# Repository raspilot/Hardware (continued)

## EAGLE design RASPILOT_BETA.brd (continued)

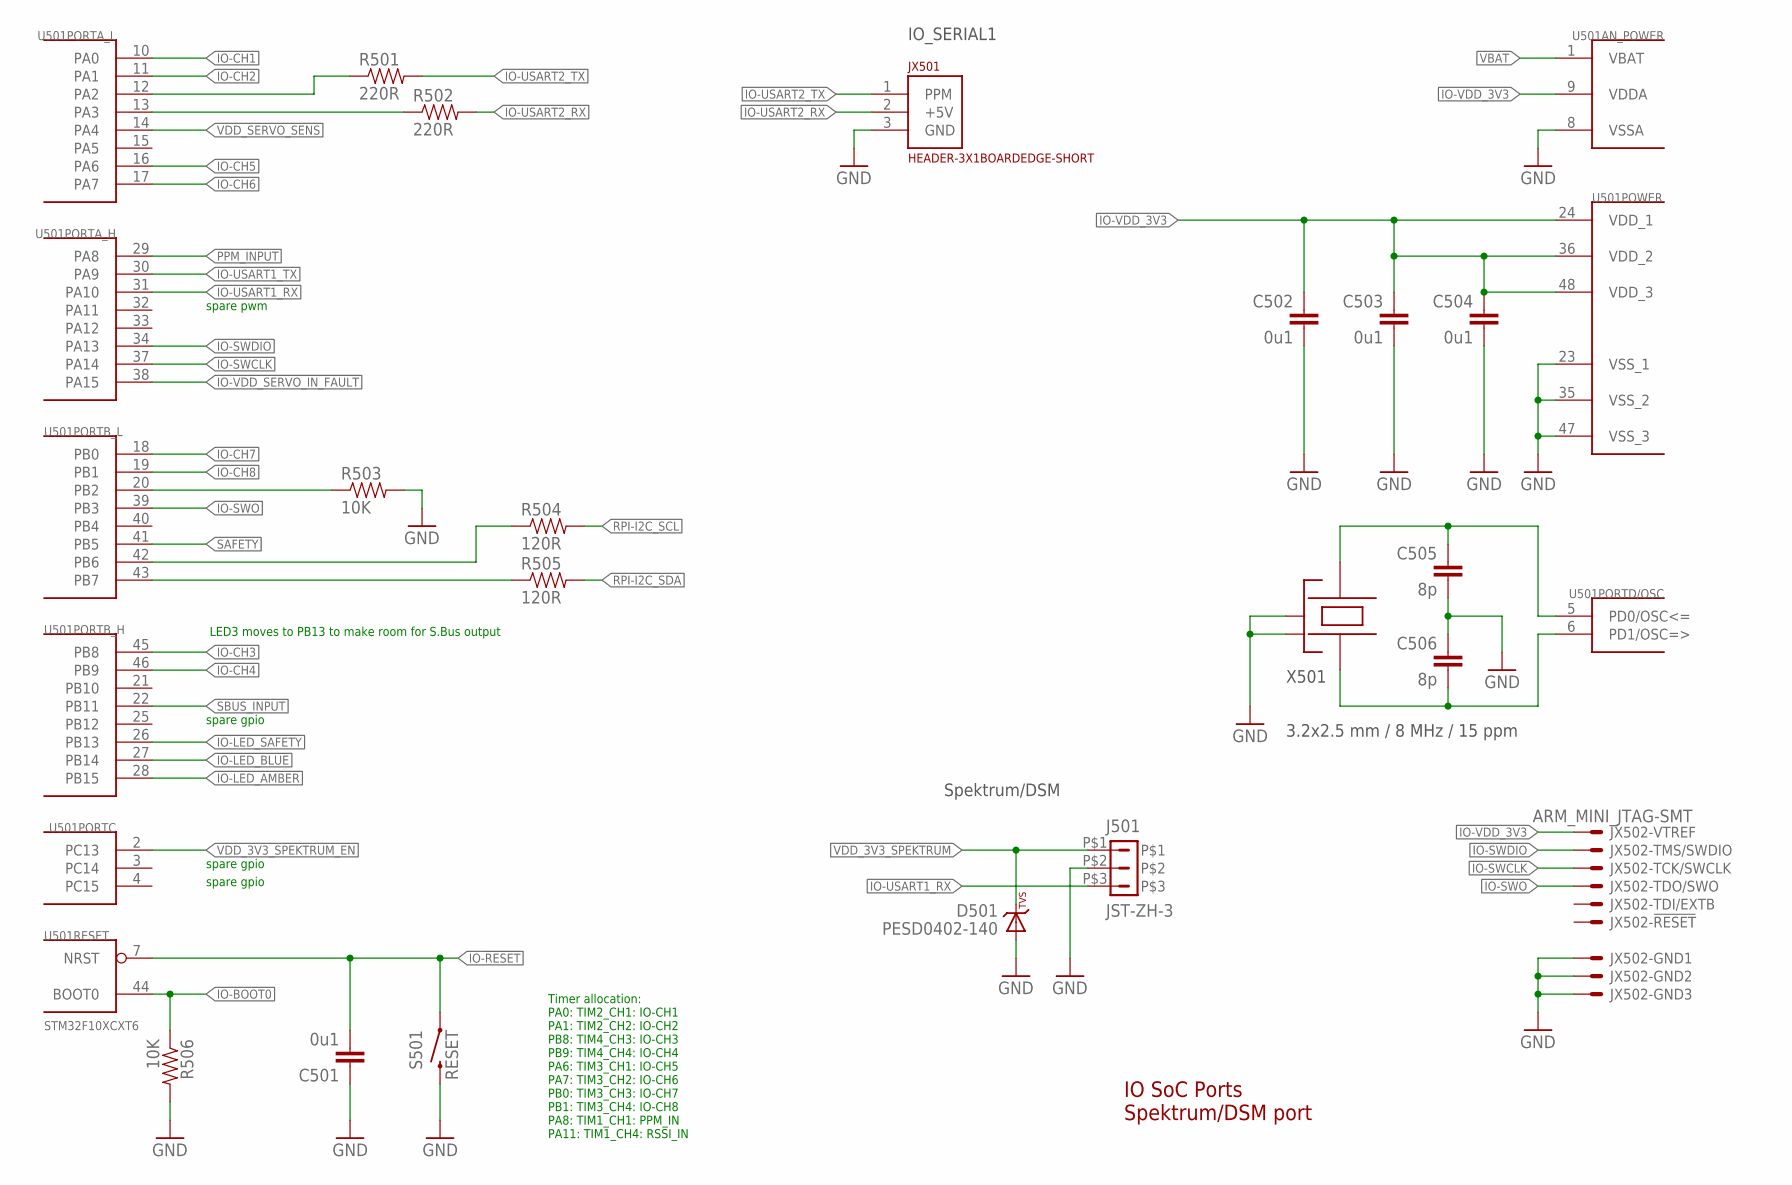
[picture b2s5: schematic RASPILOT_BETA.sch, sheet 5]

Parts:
C501, C502, C503, C504: 0u1; 0402-CAP; PARTNO CC0402ZRY5V7BB104
C505, C506: 8p; 0402-CAP; PARTNO C1005C0G1H080C
D501: PESD0402-140; 0402-TVS; PARTNO PESD0402-140
J501: JST-ZH-3; JST-ZH-SMT-VERTICAL; PARTNO B3B-ZR-SM4-TF (LF)(SN)(P)
JX501: HEADER-3X1BOARDEDGE-SHORT; HEADER_3X01_SMD_H_BOARD_EDGE_SHORT
JX502: ARM_MINI_JTAG-SMT; FTSH-105-01-XXX-DV-K; PARTNO M50-3900542
R501, R502: 220R; 0402-RES; PARTNO RC0402FR-07220RL
R503, R506: 10K; 0402-RES; PARTNO RC0402FR-0710KL
R504, R505: 120R; 0402-RES; PARTNO RC0402FR-07220RL
S501: RESET; EVQP7J01K; PARTNO EVQ-P7J01P
U501: STM32F10XCXT6; TQFP48; PARTNO STM32F100C8T6B
X501: 3.2x2.5 mm / 8 MHz / 15 ppm; OSCILLATOR-3.2X2.5; PARTNO NX3225SA-24.000000MHZ

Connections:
!IO-LED_AMBER: U501.28 (PB15); also elsewhere on the board
!IO-LED_BLUE: U501.27 (PB14); also elsewhere on the board
!IO-LED_SAFETY: U501.26 (PB13); also elsewhere on the board
GND: C501.P$1 (1), C502.P$2 (2), C503.P$2 (2), C504.P$2 (2), C505.P$2 (2), C506.P$1 (1), D501.A, J501.P$2, JX501.3 (GND), JX502.3, JX502.5, JX502.9, R503.P$2 (2), R506.P$2 (2), S501.B3 (2), U501.8 (VSSA), U501.23 (VSS_1), U501.35 (VSS_2), U501.47 (VSS_3), X501.2 (NC_2), X501.4 (NC_4); also elsewhere on the board
IO-!RESET: C501.P$2 (2), S501.A1 (1), U501.7 (NRST); also elsewhere on the board
IO-!VDD_SERVO_IN_FAULT: U501.38 (PA15); also elsewhere on the board
IO-BOOT0: R506.P$1 (1), U501.44 (BOOT0); also elsewhere on the board
IO-BOOT1: R503.P$1 (1), U501.20 (PB2)
IO-CH1: U501.10 (PA0); also elsewhere on the board
IO-CH2: U501.11 (PA1); also elsewhere on the board
IO-CH3: U501.45 (PB8); also elsewhere on the board
IO-CH4: U501.46 (PB9); also elsewhere on the board
IO-CH5: U501.16 (PA6); also elsewhere on the board
IO-CH6: U501.17 (PA7); also elsewhere on the board
IO-CH7: U501.18 (PB0); also elsewhere on the board
IO-CH8: U501.19 (PB1); also elsewhere on the board
IO-SWCLK: JX502.4, U501.37 (PA14)
IO-SWDIO: JX502.2, U501.34 (PA13)
IO-SWO: JX502.6, U501.39 (PB3)
IO-USART1_RX: J501.P$3, U501.31 (PA10)
IO-USART1_TX: U501.30 (PA9)
IO-USART2_RX: JX501.2 (+5V), R502.P$2 (2)
IO-USART2_TX: JX501.1 (PPM), R501.P$2 (2)
IO-VDD_3V3: C502.P$1 (1), C503.P$1 (1), C504.P$1 (1), JX502.1, U501.9 (VDDA), U501.24 (VDD_1), U501.36 (VDD_2), U501.48 (VDD_3); also elsewhere on the board
unnamed: R505.P$1 (1), U501.43 (PB7)
unnamed: R504.P$1 (1), U501.42 (PB6)
unnamed: C506.P$2 (2), U501.6 (PD1/OSC=>), X501.1
unnamed: C505.P$1 (1), U501.5 (PD0/OSC<=), X501.3
unnamed: R501.P$1 (1), U501.12 (PA2)
unnamed: R502.P$1 (1), U501.13 (PA3)
PPM_INPUT: U501.29 (PA8); also elsewhere on the board
RPI-I2C_SCL: R504.P$2 (2); also elsewhere on the board
RPI-I2C_SDA: R505.P$2 (2); also elsewhere on the board
SAFETY: U501.41 (PB5); also elsewhere on the board
SBUS_INPUT: U501.22 (PB11); also elsewhere on the board
VBAT: U501.1 (VBAT)
VDD_3V3_SPEKTRUM: D501.C, J501.P$1; also elsewhere on the board
VDD_3V3_SPEKTRUM_EN: U501.2 (PC13); also elsewhere on the board
VDD_SERVO_SENS: U501.14 (PA4); also elsewhere on the board

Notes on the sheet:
IO SoC Ports Spektrum/DSM port
LED3 moves to PB13 to make room for S.Bus output
IO_SERIAL1
Spektrum/DSM
Timer allocation: PA0: TIM2_CH1: IO-CH1 PA1: TIM2_CH2: IO-CH2 PB8: TIM4_CH3: IO-CH3 PB9: TIM4_CH4: IO-CH4 PA6: TIM3_CH1: IO-CH5 PA7: TIM3_CH2: IO-CH6 PB0: TIM3_CH3: IO-CH7 PB1: TIM3_CH4: IO-CH8 PA8: TIM1_CH1: PPM_IN PA11: TIM1_CH4: RSSI_IN
spare pwm
spare gpio

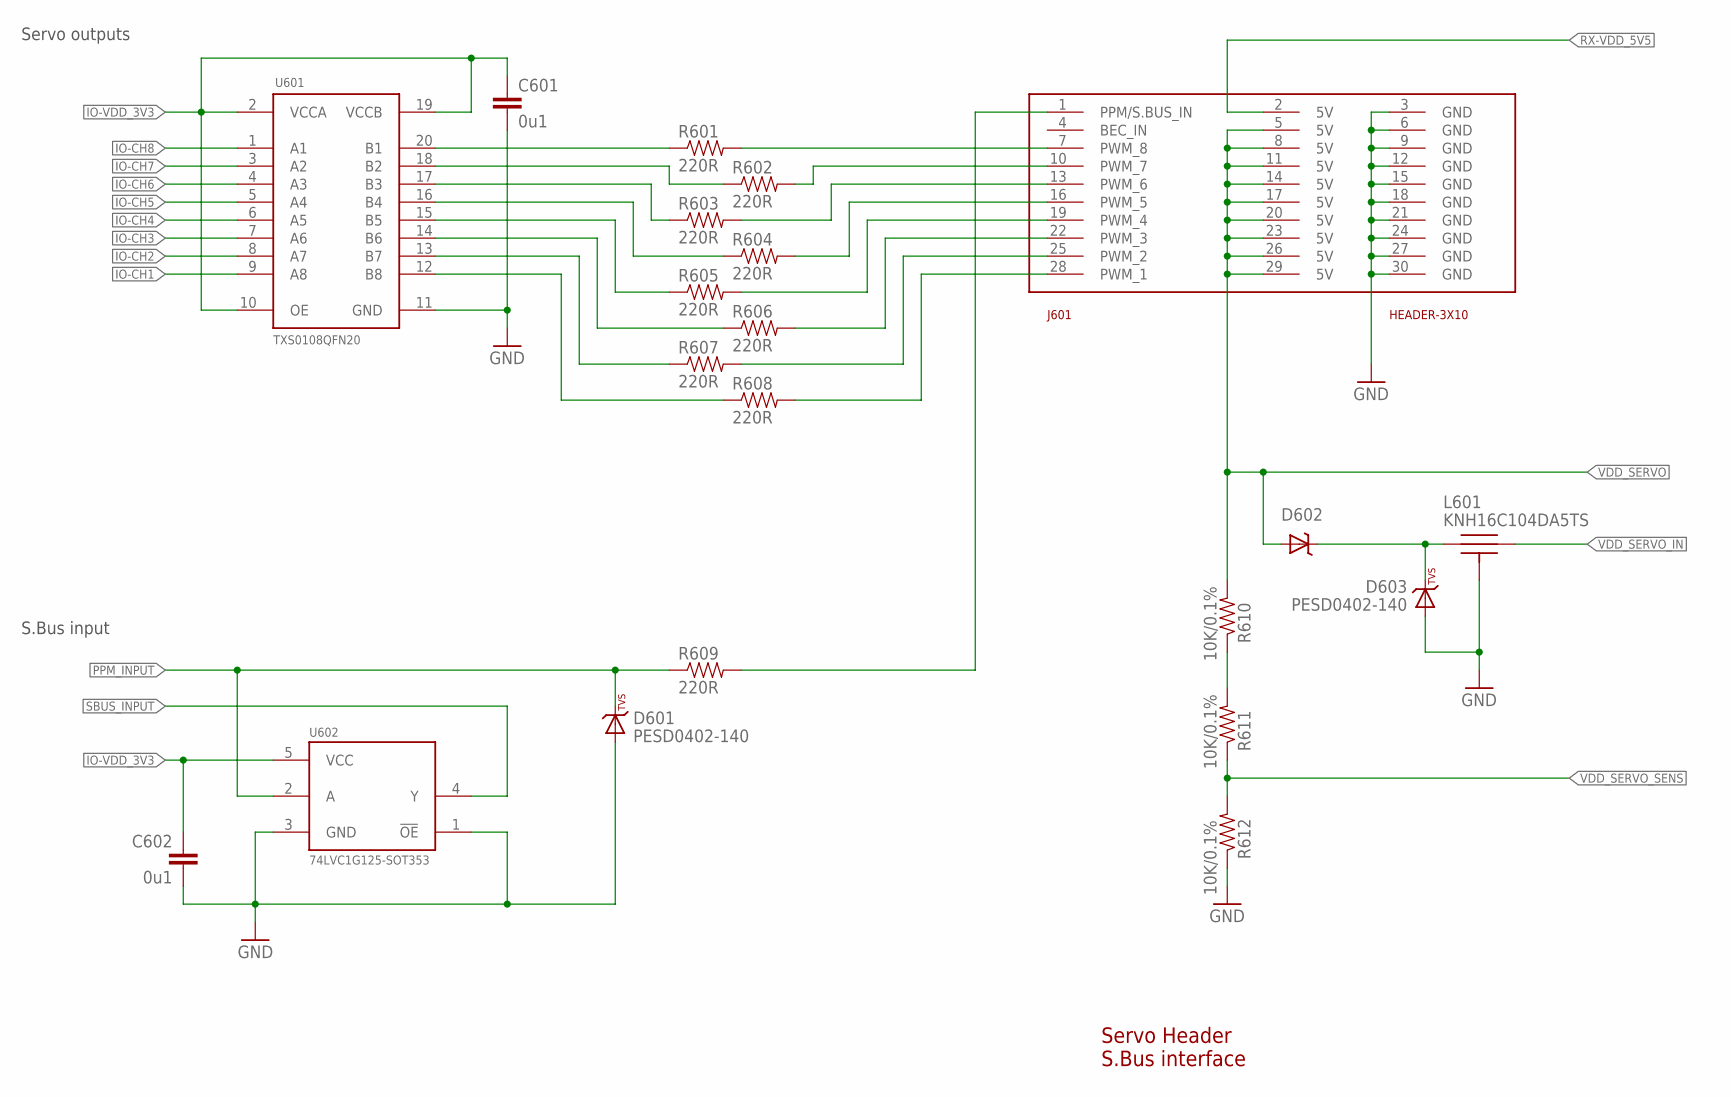
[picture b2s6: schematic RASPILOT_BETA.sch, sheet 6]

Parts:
C601, C602: 0u1; 0402-CAP; PARTNO CC0402ZRY5V7BB104
D601, D603: PESD0402-140; 0402-TVS; PARTNO PESD0402-140
D602: MSS1P4-M3; MICROSMP; PARTNO MSS1P4-M3/89A
J601: HEADER-3X10; 3X10RA
L601: KNH16C104DA5TS; KYOCERA-KNH16-DA; PARTNO KNH16C104DA5TS
R601, R602, R603, R604, R605, R606, R607, R608, R609: 220R; 0402-RES; PARTNO RC0402FR-07220RL
R610, R611, R612: 10K/0.1%; 0402-RES; PARTNO ERA-2AEB103X
U601: TXS0108QFN20; QFN20-RGY; PARTNO TXS0108ERGYR
U602: 74LVC1G125-SOT353; SOT353

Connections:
GND: C601.P$2 (2), C602.P$2 (2), D601.A, D603.A, J601.3 (GND), J601.6 (GND), J601.9 (GND), J601.12 (GND), J601.15 (GND), J601.18 (GND), J601.21 (GND), J601.24 (GND), J601.27 (GND), J601.30 (GND), L601.P$3, L601.P$4, L601.P$5, R612.P$1 (1), U601.11 (GND), U602.1 (!OE), U602.3 (GND); also elsewhere on the board
IO-CH1: U601.9 (A8); also elsewhere on the board
IO-CH2: U601.8 (A7); also elsewhere on the board
IO-CH3: U601.7 (A6); also elsewhere on the board
IO-CH4: U601.6 (A5); also elsewhere on the board
IO-CH5: U601.5 (A4); also elsewhere on the board
IO-CH6: U601.4 (A3); also elsewhere on the board
IO-CH7: U601.3 (A2); also elsewhere on the board
IO-CH8: U601.1 (A1); also elsewhere on the board
IO-VDD_3V3: C601.P$1 (1), C602.P$1 (1), U601.2 (VCCA), U601.10 (OE), U601.19 (VCCB), U602.5 (VCC); also elsewhere on the board
unnamed: R610.P$1 (1), R611.P$2 (2)
unnamed: J601.7 (PWM_8), R601.P$2 (2)
unnamed: R601.P$1 (1), U601.20 (B1)
unnamed: R602.P$1 (1), U601.18 (B2)
unnamed: R603.P$1 (1), U601.17 (B3)
unnamed: R604.P$1 (1), U601.16 (B4)
unnamed: R605.P$1 (1), U601.15 (B5)
unnamed: R606.P$1 (1), U601.14 (B6)
unnamed: R607.P$1 (1), U601.13 (B7)
unnamed: R608.P$1 (1), U601.12 (B8)
unnamed: J601.10 (PWM_7), R602.P$2 (2)
unnamed: J601.28 (PWM_1), R608.P$2 (2)
unnamed: J601.25 (PWM_2), R607.P$2 (2)
unnamed: J601.22 (PWM_3), R606.P$2 (2)
unnamed: J601.19 (PWM_4), R605.P$2 (2)
unnamed: J601.16 (PWM_5), R604.P$2 (2)
unnamed: J601.13 (PWM_6), R603.P$2 (2)
unnamed: D602.CATHODE (C), D603.C, L601.P$1
PPM-SBUS-PROT: J601.1 (PPM/S.BUS_IN), R609.P$2 (2)
PPM_INPUT: D601.C, R609.P$1 (1), U602.2 (A); also elsewhere on the board
RX-VDD_5V5: J601.2 (5V); also elsewhere on the board
SBUS_INPUT: U602.4 (Y); also elsewhere on the board
VDD_SERVO: D602.ANODE (A), J601.5 (5V), J601.8 (5V), J601.11 (5V), J601.14 (5V), J601.17 (5V), J601.20 (5V), J601.23 (5V), J601.26 (5V), J601.29 (5V), R610.P$2 (2); also elsewhere on the board
VDD_SERVO_IN: L601.P$2; also elsewhere on the board
VDD_SERVO_SENS: R611.P$1 (1), R612.P$2 (2); also elsewhere on the board

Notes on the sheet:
Servo Header S.Bus interface
S.Bus input
Servo outputs

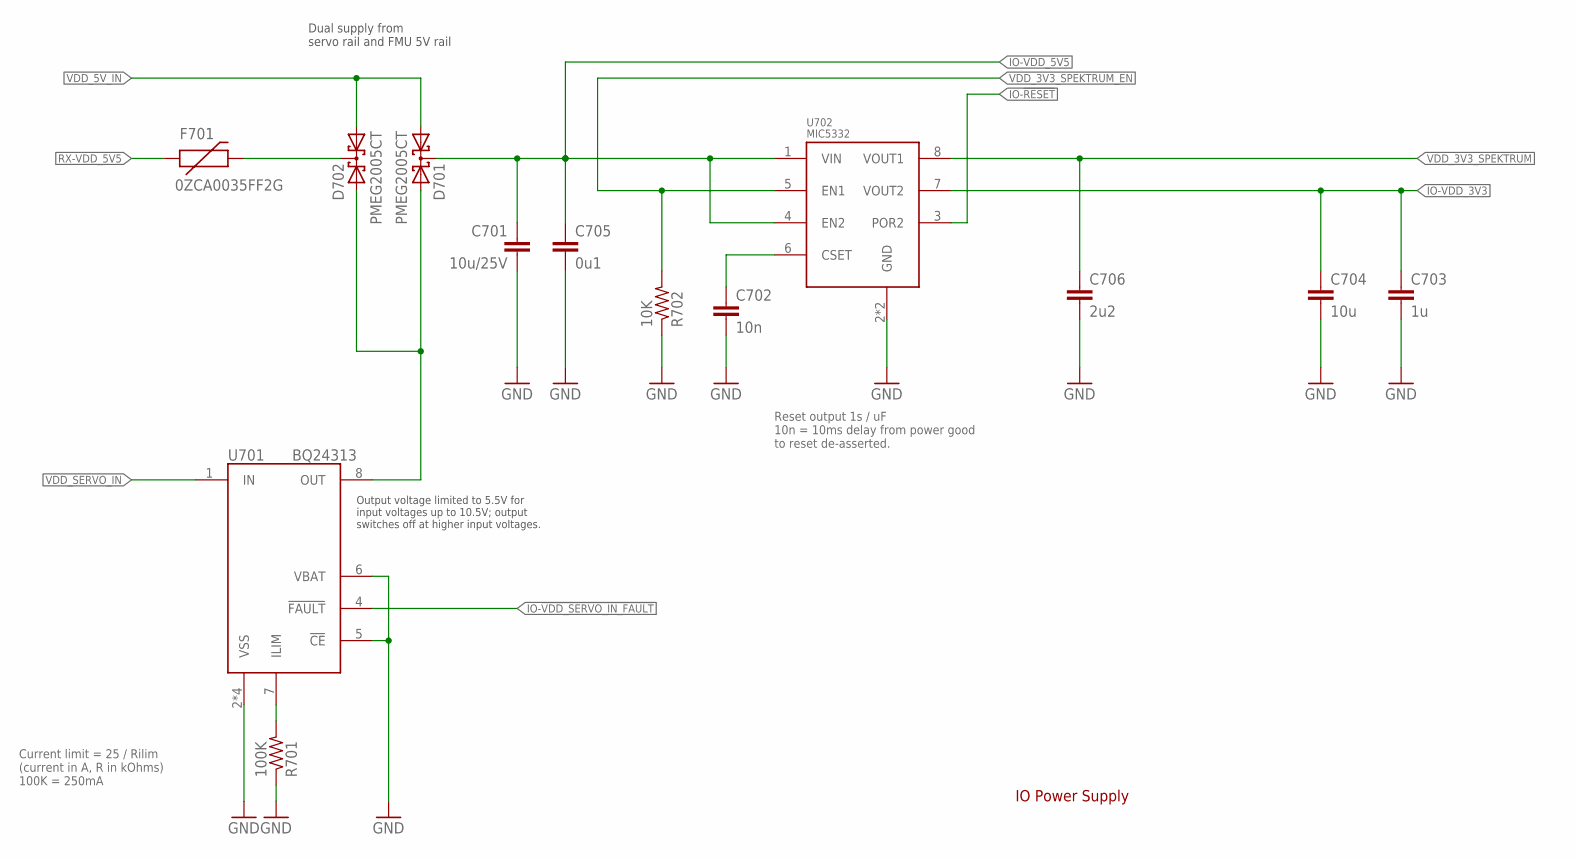
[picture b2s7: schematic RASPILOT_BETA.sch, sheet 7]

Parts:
C701: 10u/25V; 0805-CAP; PARTNO CL21A106KAYNNNE
C702: 10n; 0402-CAP; PARTNO CC0402KRX7R7BB103
C703: 1u; 0603-CAP; PARTNO CC0603ZRY5V7BB105
C704: 10u; 0603-CAP; PARTNO C1608X5R1A106K080AC
C705: 0u1; 0402-CAP; PARTNO CC0402ZRY5V7BB104
C706: 2u2; 0402-CAP; PARTNO C1005X6S1C225K050BC
D701, D702: PMEG2005CT; SOT23-3; PARTNO PMEG2005CT
F701: 0ZCA0035FF2G; PTC-1206; PARTNO 0ZCA0035FF2G
R701: 100K; 0402-RES; PARTNO RC0402FR-07100KL
R702: 10K; 0402-RES; PARTNO RC0402FR-0710KL
U701: BQ24313; QFN8-DSG; PARTNO BQ24313DSGT
U702: MIC5332; MLF-8-EPAD; PARTNO MIC5332-SSYMT

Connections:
GND: C701.P$2 (2), C702.P$2 (2), C703.P$2 (2), C704.P$2 (2), C705.P$2 (2), C706.P$2 (2), R701.P$1 (1), R702.P$1 (1), U701.2 (VSS), U701.5 (!CE), U701.6 (VBAT), U701.GND (VSS), U701.P$2 (VSS), U701.P$3 (VSS), U702.2 (GND), U702.GND; also elsewhere on the board
IO-!RESET: U702.3 (POR2); also elsewhere on the board
IO-!VDD_SERVO_IN_FAULT: U701.4 (!FAULT); also elsewhere on the board
IO-VDD_3V3: C703.P$1 (1), C704.P$1 (1), U702.7 (VOUT2); also elsewhere on the board
IO-VDD_5V5: C701.P$1 (1), C705.P$1 (1), D701.3 (CC), U702.1 (VIN), U702.4 (EN2); also elsewhere on the board
unnamed: D701.2 (A2), D702.2 (A2), U701.8 (OUT)
unnamed: R701.P$2 (2), U701.7 (ILIM)
unnamed: D702.3 (CC), F701.2
unnamed: C702.P$1 (1), U702.6 (CSET)
RX-VDD_5V5: F701.1; also elsewhere on the board
VDD_3V3_SPEKTRUM: C706.P$1 (1), U702.8 (VOUT1); also elsewhere on the board
VDD_3V3_SPEKTRUM_EN: R702.P$2 (2), U702.5 (EN1); also elsewhere on the board
VDD_5V_IN: D701.1 (A1), D702.1 (A1); also elsewhere on the board
VDD_SERVO_IN: U701.1 (IN); also elsewhere on the board

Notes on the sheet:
Dual supply from servo rail and FMU 5V rail
Current limit = 25 / Rilim (current in A, R in kOhms) 100K = 250mA
IO Power Supply
Reset output 1s / uF 10n = 10ms delay from power good to reset de-asserted.
Output voltage limited to 5.5V for input voltages up to 10.5V; output switches off at higher input voltages.

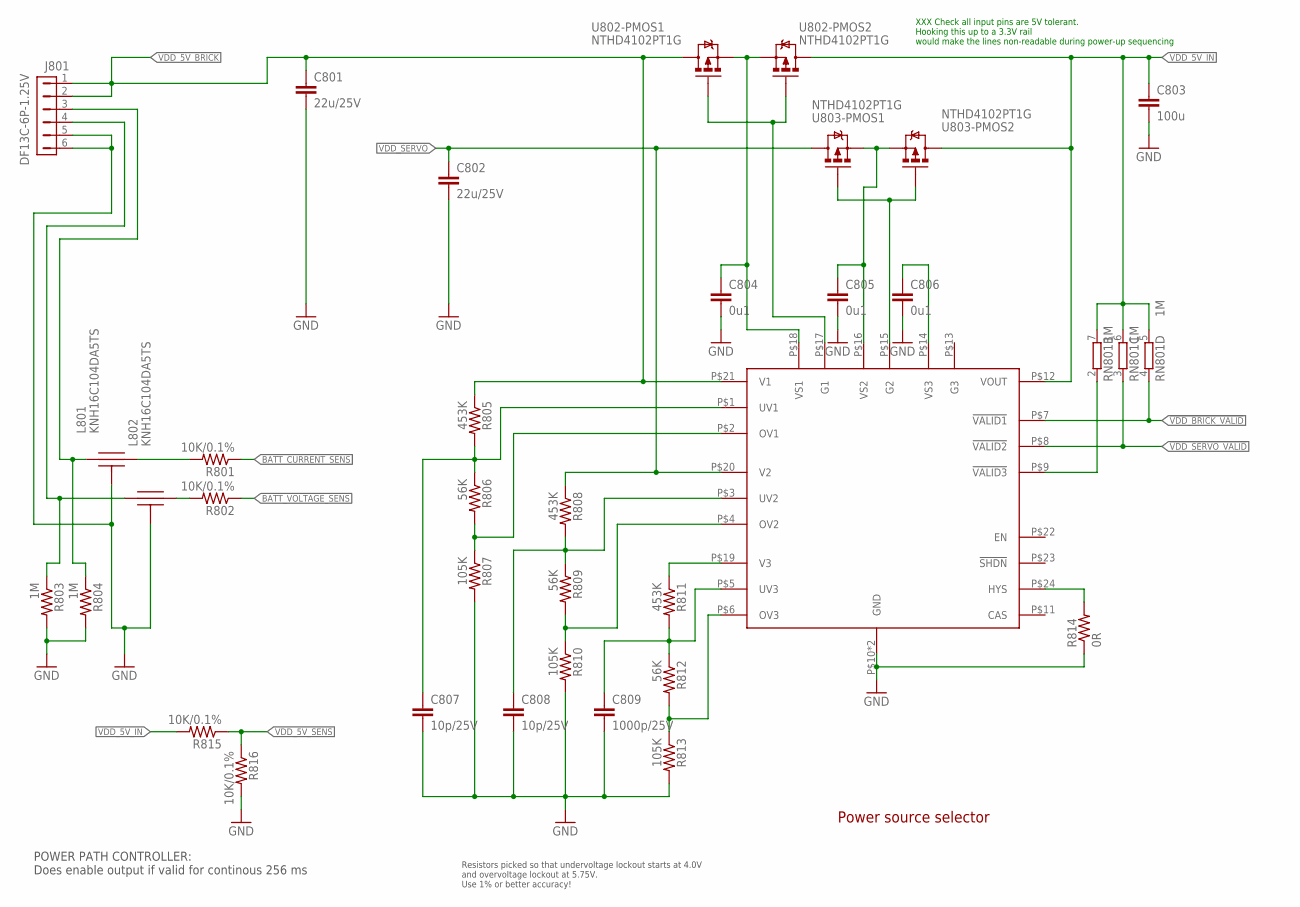
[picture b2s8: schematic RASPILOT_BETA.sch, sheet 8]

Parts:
C801, C802: 22u/25V; 0805-CAP; PARTNO CL21A226MAQNNNE
C803: 100u; 1206-CAP; PARTNO C3216X5R1A107M160AC
C804, C805, C806: 0u1; 0402-CAP; PARTNO C1005X7R1E104K050BB
C807, C808: 10p/25V; 0402-CAP; PARTNO C0402C100J3GACTU
C809: 1000p/25V; 0402-CAP; PARTNO GRM1555C1E102JA01D
J801: DF13C-6P-1.25V; PARTNO DF13C-6P-1.25V(20)
L801, L802: KNH16C104DA5TS; KYOCERA-KNH16-DA; PARTNO KNH16C104DA5TS
R801, R802, R815, R816: 10K/0.1%; 0402-RES; PARTNO ERA-2AEB103X
R803, R804: 1M; 0402-RES; PARTNO RC0402FR-071ML
R805, R808, R811: 453K; 0402-RES; PARTNO RMCF0402FT453K
R806, R809, R812: 56K; 0402-RES; PARTNO ERA-2AEB563X
R807, R810, R813: 105K; 0402-RES; PARTNO ERJ-2RKF1053X
R814: 0R; 0402-RES; PARTNO ERJ-2GE0R00X
RN801: 1M; EXB28V; PARTNO EXB-28V105JX
U801: LTC4417; MO-220; PARTNO LTC4417IUF#PBF
U802, U803: NTHD4102PT1G; 1206-8; PARTNO NTHD4102PT1G

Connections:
!VDD_BRICK_VALID: RN801.4 (1), U801.P$7 (!VALID1); also elsewhere on the board
!VDD_SERVO_VALID: RN801.3 (1), U801.P$8 (!VALID2); also elsewhere on the board
BATT_CURRENT_SENS: R801.P$1 (1); also elsewhere on the board
BATT_CURRENT_SENS_PROT: J801.3, L801.P$1, R804.P$1 (1)
BATT_VOLTAGE_SENS: R802.P$1 (1); also elsewhere on the board
BATT_VOLTAGE_SENS_PROT: J801.4, L802.P$1, R803.P$1 (1)
GND: C801.P$2 (2), C802.P$2 (2), C803.P$2 (2), C804.P$2 (2), C805.P$2 (2), C806.P$2 (2), C807.P$2 (2), C808.P$2 (2), C809.P$2 (2), J801.5, J801.6, L801.P$3, L801.P$4, L801.P$5, L802.P$3, L802.P$4, L802.P$5, R803.P$2 (2), R804.P$2 (2), R807.P$2 (2), R810.P$2 (2), R813.P$2 (2), R814.P$1 (1), R816.P$2 (2), U801.P$10 (GND), U801.P$25 (GND); also elsewhere on the board
unnamed: C807.P$1 (1), R805.P$2 (2), R806.P$1 (1), U801.P$1 (UV1)
unnamed: R806.P$2 (2), R807.P$1 (1), U801.P$2 (OV1)
unnamed: C808.P$1 (1), R808.P$2 (2), R809.P$1 (1), U801.P$3 (UV2)
unnamed: R809.P$2 (2), R810.P$1 (1), U801.P$4 (OV2)
unnamed: R812.P$2 (2), R813.P$1 (1), U801.P$6 (OV3)
unnamed: C809.P$1 (1), R811.P$2 (2), R812.P$1 (1), U801.P$5 (UV3)
unnamed: RN801.2 (1), U801.P$9 (!VALID3)
unnamed: C804.P$1 (1), U801.P$18 (VS1), U802.P$1 (S), U802.P$3 (S)
unnamed: L802.P$2, R802.P$2 (2)
unnamed: L801.P$2, R801.P$2 (2)
unnamed: R814.P$2 (2), U801.P$24 (HYS)
unnamed: C805.P$1 (1), U801.P$16 (VS2), U803.P$1 (S), U803.P$3 (S)
unnamed: C806.P$1 (1), U801.P$14 (VS3)
unnamed: U801.P$15 (G2), U803.P$2 (G), U803.P$4 (G)
unnamed: U801.P$17 (G1), U802.P$2 (G), U802.P$4 (G)
VBUS: R811.P$1 (1), U801.P$19 (V3)
VDD_5V_BRICK: C801.P$1 (1), J801.1, J801.2, R805.P$1 (1), U801.P$21 (V1), U802.P$7 (D), U802.P$8 (D); also elsewhere on the board
VDD_5V_IN: C803.P$1 (1), R815.P$2 (2), RN801.5 (2), RN801.6 (2), RN801.7 (2), U801.P$12 (VOUT), U802.P$5 (D), U802.P$6 (D), U803.P$5 (D), U803.P$6 (D); also elsewhere on the board
VDD_5V_SENS: R815.P$1 (1), R816.P$1 (1); also elsewhere on the board
VDD_SERVO: C802.P$1 (1), R808.P$1 (1), U801.P$20 (V2), U803.P$7 (D), U803.P$8 (D); also elsewhere on the board

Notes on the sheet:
Power source selector
Resistors picked so that undervoltage lockout starts at 4.0V and overvoltage lockout at 5.75V. Use 1% or better accuracy!
POWER PATH CONTROLLER: Does enable output if valid for continous 256 ms
XXX Check all input pins are 5V tolerant. Hooking this up to a 3.3V rail would make the lines non-readable during power-up sequencing

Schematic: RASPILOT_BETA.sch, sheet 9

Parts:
!VDD_BRICK_VALID: PAD.04; PAD.04X.04; PARTNO *
!VDD_SERVO_VALID: PAD.04; PAD.04X.04; PARTNO *
GND, GND.: PAD.04; PAD.04X.04; PARTNO *
IO-BOOT0: PAD.04; PAD.04X.04; PARTNO *
JP1, JP2: FIDUCIAL1.5X3; FIDUCIAL-1.5X3; PARTNO *
M3_MOUNT1101, M3_MOUNT1102, M3_MOUNT1103, M3_MOUNT1104: MOUNT-HOLE3.1MM; MOUNT-HOLE3.1; PARTNO *
OSHW_LOGO: OSHW-LOGOS; OSHW-LOGO-S; PARTNO *
RPI_AUX_ADC: PAD.04; PAD.04X.04; PARTNO *
S1RX, S1TX: PAD.04; PAD.04X.04; PARTNO *
VDD_3V3, VDD_5V_BRICK, VDD_5V_IN: PAD.04; PAD.04X.04; PARTNO *
VDD_SERVO: PAD.04; PAD.04X.04; PARTNO *

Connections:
!VDD_BRICK_VALID: !VDD_BRICK_VALID.P$1; also elsewhere on the board
!VDD_SERVO_VALID: !VDD_SERVO_VALID.P$1; also elsewhere on the board
GND: GND.P$1, GND..P$1; also elsewhere on the board
IO-BOOT0: IO-BOOT0.P$1; also elsewhere on the board
RPI-VDD_3V3: VDD_3V3.P$1; also elsewhere on the board
RPI_AUX_ADC1: RPI_AUX_ADC.P$1; also elsewhere on the board
SERIAL1_RX: S1RX.P$1; also elsewhere on the board
SERIAL1_TX: S1TX.P$1; also elsewhere on the board
VDD_5V_BRICK: VDD_5V_BRICK.P$1; also elsewhere on the board
VDD_5V_IN: VDD_5V_IN.P$1; also elsewhere on the board
VDD_SERVO: VDD_SERVO.P$1; also elsewhere on the board

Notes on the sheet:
Mounting holes to suit M3 fastener
and Richco R908 series spacer.
Use R908-5 spacers to stack with
other PX4 series boards (7.95 mm).
Production Testing Pads
Test and Fiducials
Minimum drill: 0.3 mm
Minimum trace width (use mm for traces): 0.15 mm
Minimum copper distance (all signals): 0.15 mm
Dimension / hole minimum distance: 0.2 mm
Layout grid: 4 mil, part grid: 4 mil. Dimensions / hole positions: 0.5 mm
Board: FR4 black, 1.0 mm. Solder stop on vias < 0.6 mm.
Signoff rules: Footprint checked, pinmap checked, schematic checked, cross-references to other pages checked.
Routing: 1: general/escape 2: ground 3: horizontal 4: vertical 5: power 6: general/escape
Fiducials for machine vision alignment.
Parts: Resistors: 0402 / 1% unless specified otherwise Capacitors: 0402 to 1206, ceramic, voltage rating: 10V unless specified
COMMS
POWER
STATUS AND ANALOG

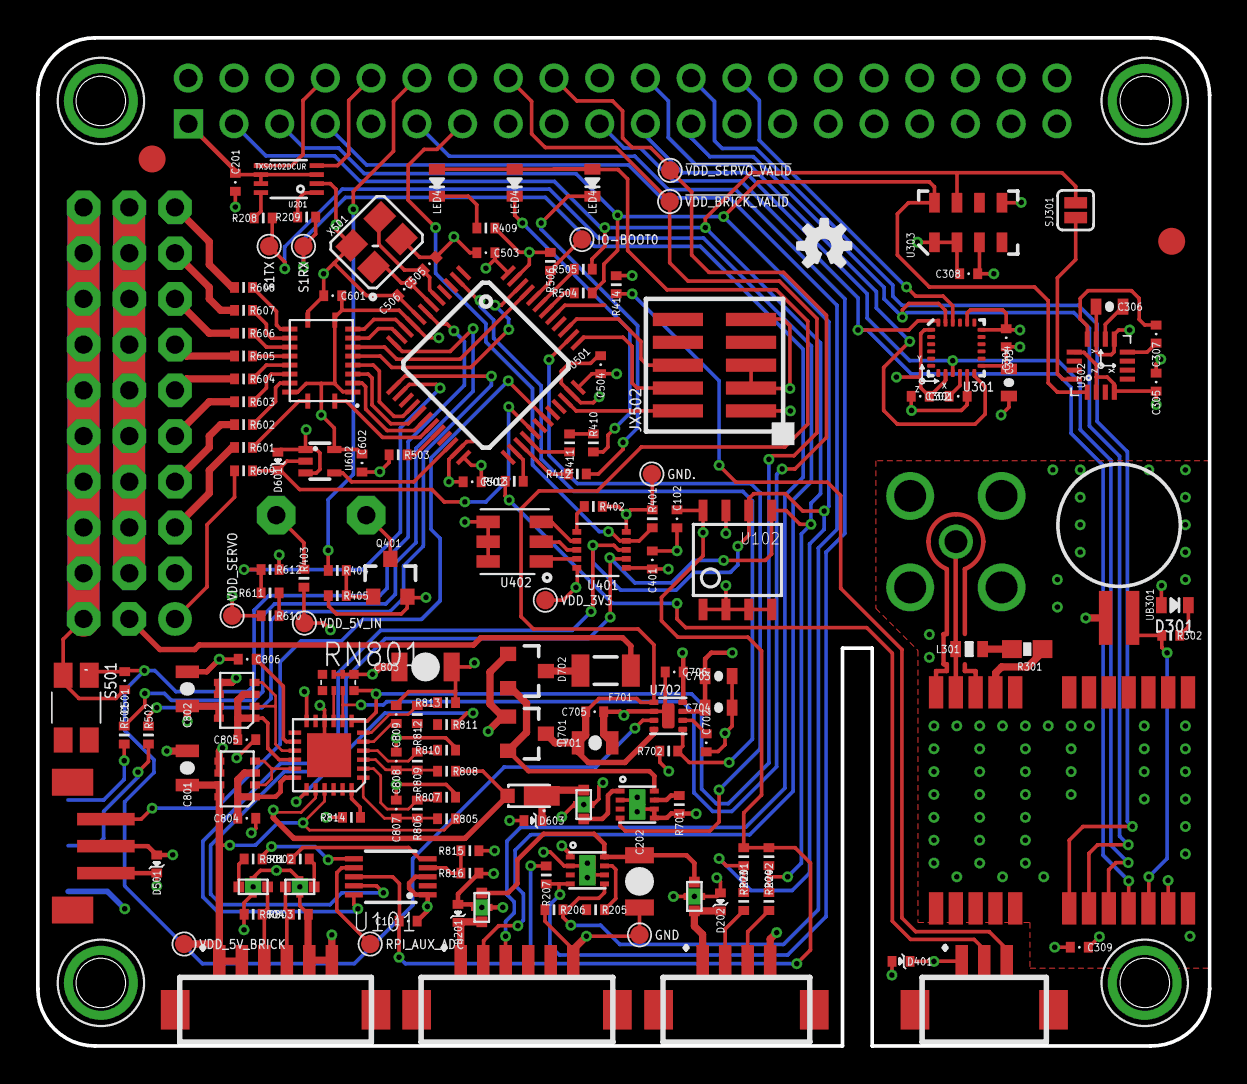
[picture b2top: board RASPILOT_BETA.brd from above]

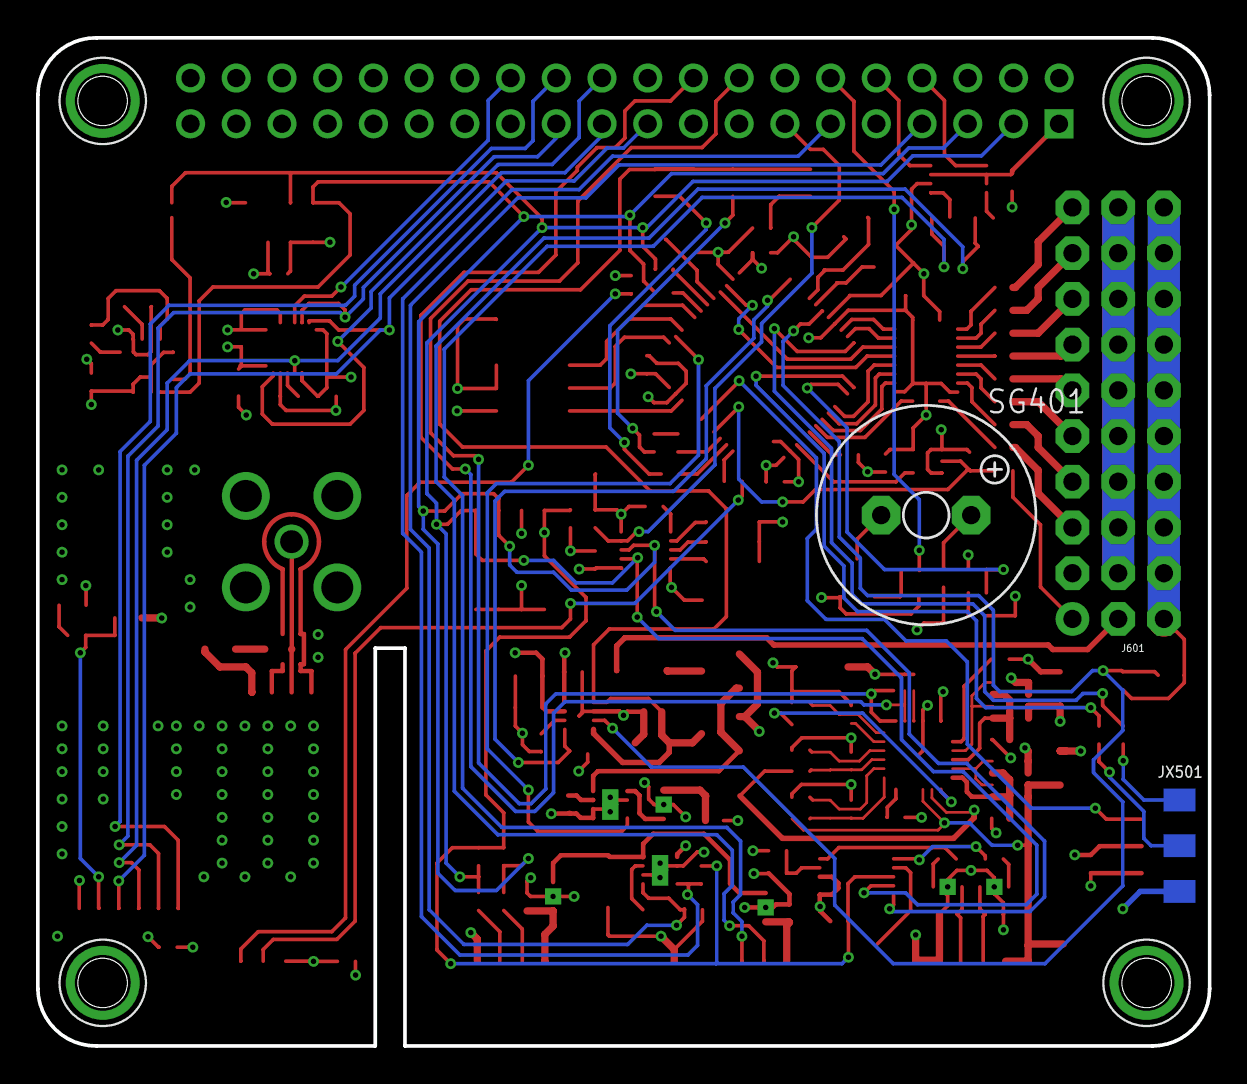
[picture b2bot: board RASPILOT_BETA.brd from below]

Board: 4 copper layers, 65.1 x 56.0 mm, 169 parts (3 on the bottom side), 135 nets.

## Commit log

2015-05-23 new file: RASPILOT_BETA.brd new file: RASPILOT_BETA.sch
2015-07-09 new file: RASPILOTv1_0.brd new file: RASPILOTv1_0.sch
2015-07-09 new file: pixhawk2.lbr
2015-08-12 new file: RASPILOTv1_0.pdf new file: RASPILOTv1_1.brd new file: RASPILOTv1_1.pdf new file: RASPILOTv1_1.sch
